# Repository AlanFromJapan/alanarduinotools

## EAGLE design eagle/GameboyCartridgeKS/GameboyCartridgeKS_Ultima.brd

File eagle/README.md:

The content of this folder was moved to another repository for clarity reason on May 29th 2020.
On the same Git account, the repository is **pcb-design**.

Here : https://github.com/AlanFromJapan/pcb-design

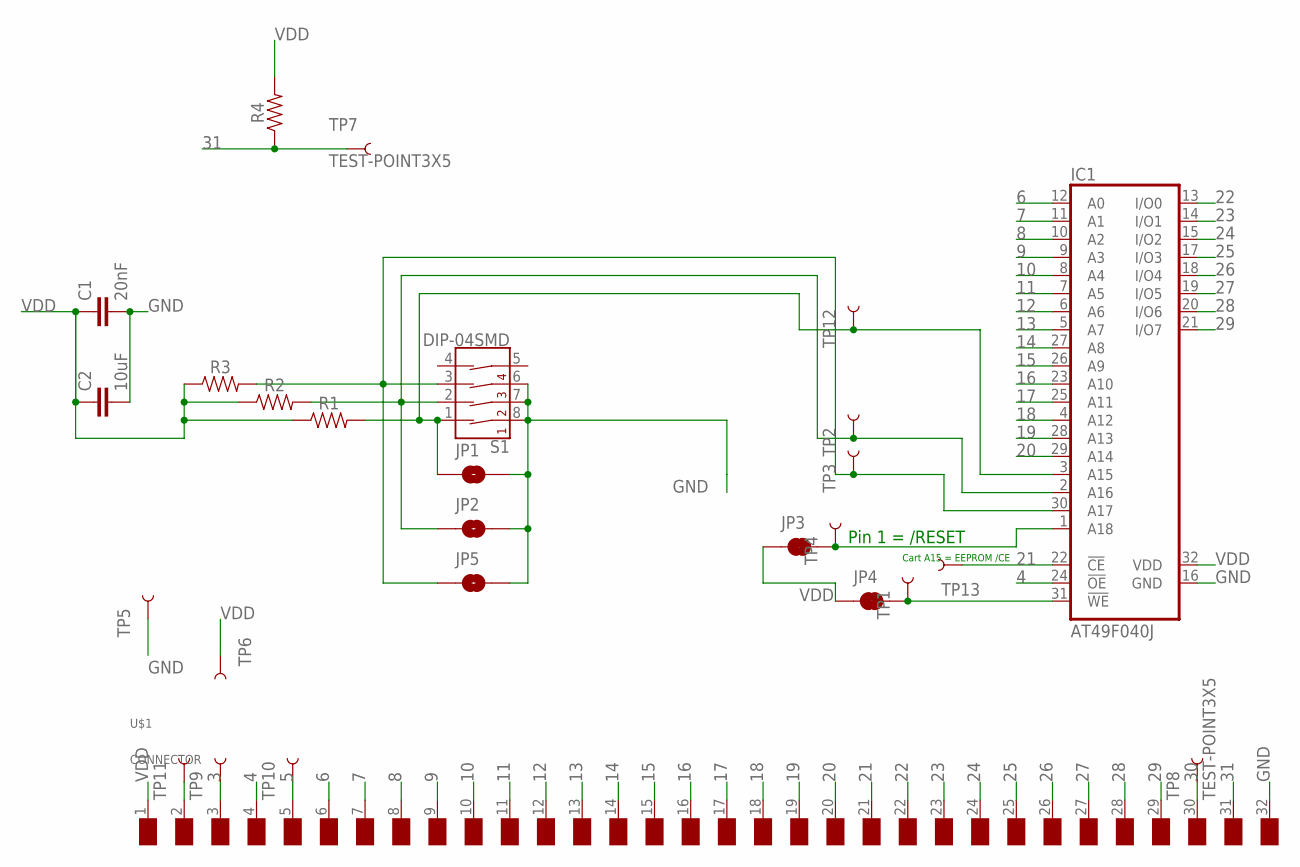
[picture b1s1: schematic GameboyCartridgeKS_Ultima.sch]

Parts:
C1: 20nF; C0805
C2: 10uF; 1206
IC1: AT49F040J; PLCC32R
JP1, JP2, JP5: JUMPER-SMT_2_NO_NO-SILK; SMT-JUMPER_2_NO_NO-SILK
JP3, JP4: JUMPER-SMT_2_NC_TRACE_SILK; SMT-JUMPER_2_NC_TRACE_SILK
R1, R2, R3, R4: 1206
S1: DIP-04SMD; DIPSWITCH-04-SMD
TP1, TP2, TP3, TP4, TP5, TP6, TP7, TP8, TP9, TP10, TP11, TP12, TP13: TEST-POINT3X5; PAD.03X.05
U$1: CONNECTOR

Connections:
3: TP9.P$1, U$1.3 (/WR)
4: IC1.24 (!OE), U$1.4 (/RD)
5: TP10.P$1, U$1.5 (/RCS)
6: IC1.12 (A0), U$1.6 (A0)
7: IC1.11 (A1), U$1.7 (A1)
8: IC1.10 (A2), U$1.8 (A2)
9: IC1.9 (A3), U$1.9 (A3)
10: IC1.8 (A4), U$1.10 (A4)
11: IC1.7 (A5), U$1.11 (A5)
12: IC1.6 (A6), U$1.12 (A6)
13: IC1.5 (A7), U$1.13 (A7)
14: IC1.27 (A8), U$1.14 (A8)
15: IC1.26 (A9), U$1.15 (A9)
16: IC1.23 (A10), U$1.16 (A10)
17: IC1.25 (A11), U$1.17 (A11)
18: IC1.4 (A12), U$1.18 (A12)
19: IC1.28 (A13), U$1.19 (A13)
20: IC1.29 (A14), U$1.20 (A14)
21: IC1.22 (!CE), TP13.P$1, U$1.21 (A15)
22: IC1.13 (I/O0), U$1.22 (D0)
23: IC1.14 (I/O1), U$1.23 (D1)
24: IC1.15 (I/O2), U$1.24 (D2)
25: IC1.17 (I/O3), U$1.25 (D3)
26: IC1.18 (I/O4), U$1.26 (D4)
27: IC1.19 (I/O5), U$1.27 (D5)
28: IC1.20 (I/O6), U$1.28 (D6)
29: IC1.21 (I/O7), U$1.29 (D7)
30: TP8.P$1, U$1.30 (/RS)
31: R4.1, TP7.P$1, U$1.31 (VIN)
GND: C1.2, C2.2, IC1.16 (GND), JP1.2, JP2.2, JP5.2, S1.6 (3B), S1.7 (2B), S1.8 (1B), TP5.P$1, U$1.32 (GND)
unnamed: IC1.31 (!WE), JP4.2, TP1.P$1
unnamed: TP11.P$1, U$1.2 (NC)
unnamed: IC1.3 (A15), JP1.1, R1.2, S1.1 (1A), TP12.P$1
unnamed: IC1.1 (A18), JP3.2, TP4.P$1
unnamed: IC1.2 (A16), JP2.1, R2.2, S1.2 (2A), TP2.P$1
unnamed: IC1.30 (A17), JP5.1, R3.2, S1.3 (3A), TP3.P$1
VDD: C1.1, C2.1, IC1.32 (VDD), JP3.1, JP4.1, R1.1, R2.1, R3.1, R4.2, TP6.P$1, U$1.1 (VDD)

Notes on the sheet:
Pin 1 = /RESET
Cart A15 = EEPROM /CE

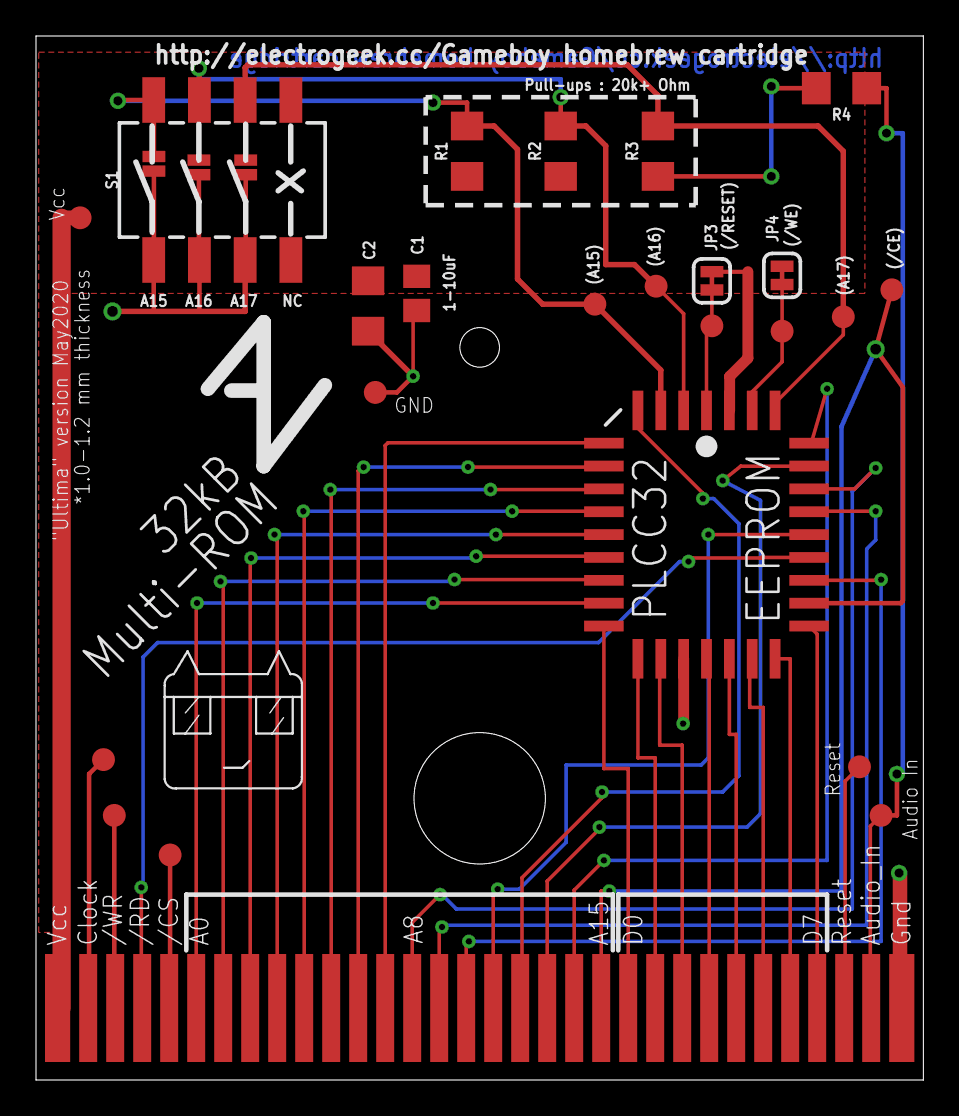
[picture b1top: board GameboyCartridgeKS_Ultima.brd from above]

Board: 2 copper layers, 49.3 x 58.0 mm, 29 parts (0 on the bottom side), 37 nets.

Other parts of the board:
U$2: GAMEBOY_LOGO
U$3: PIGMAN1

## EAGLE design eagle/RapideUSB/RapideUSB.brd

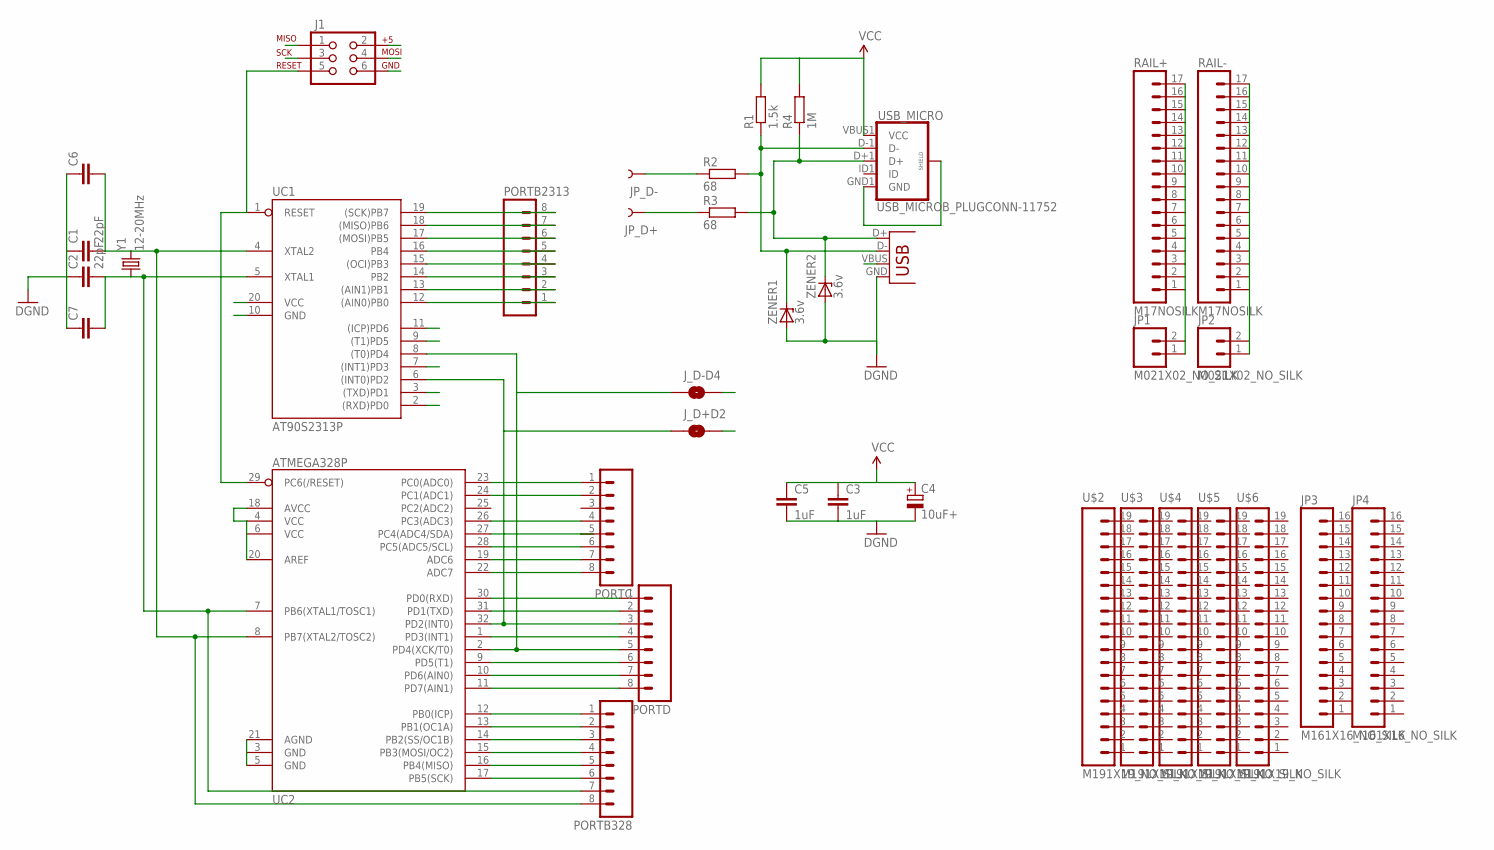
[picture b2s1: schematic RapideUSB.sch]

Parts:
C1, C2: 22pF; C025-024X044
C3, C5: 1uF; C025-024X044
C4: 10uF+; E2-5
C6, C7: C-EUC1206K; C1206K
J1: AVR_SPI_PRG_6PTH; 2X3
JP1, JP2: M021X02_NO_SILK; 1X02_NO_SILK
JP3, JP4: M161X16_NO_SILK; 1X16_NO_SILK
JP_D+: TEST-POINT3X5; PAD.03X.05
JP_D-: TEST-POINT3X5; PAD.03X.05
J_D+D2: JUMPER-PAD-2-NOYES_SILK; PAD-JUMPER-2-NO_YES_SILK
J_D-D4: JUMPER-PAD-2-NOYES_SILK; PAD-JUMPER-2-NO_YES_SILK
PORTB328, PORTB2313: M081X08; 1X08
PORTC: M081X08; 1X08
PORTD: M081X08; 1X08
R1: 1.5k; 0204V
R2, R3: 68; 0204V
R4: 1M; 0204V
RAIL+: M17NOSILK; 1X17_NO_SILK
RAIL-: M17NOSILK; 1X17_NO_SILK
U$2, U$3, U$4, U$5, U$6: M191X19_NO_SILK; 1X19_NO_SILK
UC1: AT90S2313P; DIL20
UC2: ATMEGA328P; TQFP32-08
USB_MICRO: USB_MICROB_PLUGCONN-11752; USB-B-MICRO-SMD_V03
USB_MINI: USBSMD; USB-MINIB
Y1: 12-20MHz; HC49U-V
ZENER1, ZENER2: 3.6v; ZDIO-2.5

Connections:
B0: PORTB328.1, UC2.12 (PB0(ICP))
B1: PORTB328.2, UC2.13 (PB1(OC1A))
B2: PORTB328.3, UC2.14 (PB2(SS/OC1B))
B6: C2.2, C7.2, PORTB328.7, UC1.5 (XTAL1), UC2.7 (PB6(XTAL1/TOSC1)), Y1.1
B7: C1.2, C6.2, PORTB328.8, UC1.4 (XTAL2), UC2.8 (PB7(XTAL2/TOSC2)), Y1.2
D0: PORTD.1, UC1.2 ((RXD)PD0), UC2.30 (PD0(RXD))
D1: PORTD.2, UC1.3 ((TXD)PD1), UC2.31 (PD1(TXD))
D2: J_D+D2.1, PORTD.3, UC1.6 ((INT0)PD2), UC2.32 (PD2(INT0))
D3: PORTD.4, UC1.7 ((INT1)PD3), UC2.1 (PD3(INT1))
D4: J_D-D4.1, PORTD.5, UC1.8 ((T0)PD4), UC2.2 (PD4(XCK/T0))
D5: PORTD.6, UC1.9 ((T1)PD5), UC2.9 (PD5(T1))
D6: PORTD.7, UC1.11 ((ICP)PD6), UC2.10 (PD6(AIN0))
D7: PORTD.8, UC2.11 (PD7(AIN1))
D+: JP_D+.P$1, J_D+D2.2, R3.1
D-: JP_D-.P$1, J_D-D4.2, R2.1
GND: C1.1, C2.1, C3.2, C4.-, C5.2, C6.1, C7.1, J1.6, JP2.1, JP2.2, RAIL-.1, RAIL-.2, RAIL-.3, RAIL-.4, RAIL-.5, RAIL-.6, RAIL-.7, RAIL-.8, RAIL-.9, RAIL-.10, RAIL-.11, RAIL-.12, RAIL-.13, RAIL-.14, RAIL-.15, RAIL-.16, RAIL-.17, UC1.10 (GND), UC2.3 (GND), UC2.5 (GND), UC2.21 (AGND), USB_MICRO.GND1 (GND), USB_MICRO.SHIELD1 (SHIELD), USB_MICRO.SHIELD2 (SHIELD), USB_MICRO.SHIELD3 (SHIELD), USB_MINI.GND, ZENER1.A, ZENER2.A
MISO: J1.1, PORTB328.5, PORTB2313.7, UC1.18 ((MISO)PB6), UC2.16 (PB4(MISO))
MOSI: J1.4, PORTB328.4, PORTB2313.6, UC1.17 ((MOSI)PB5), UC2.15 (PB3(MOSI/OC2))
unnamed: PORTB2313.5, UC1.16 (PB4)
unnamed: PORTB2313.4, UC1.15 ((OCI)PB3)
unnamed: PORTB2313.3, UC1.14 (PB2)
unnamed: PORTB2313.2, UC1.13 ((AIN1)PB1)
unnamed: PORTC.1, UC2.23 (PC0(ADC0))
unnamed: PORTC.2, UC2.24 (PC1(ADC1))
unnamed: PORTC.4, UC2.26 (PC3(ADC3))
unnamed: PORTC.5, UC2.27 (PC4(ADC4/SDA))
unnamed: PORTC.6, UC2.28 (PC5(ADC5/SCL))
unnamed: PORTC.7, UC2.19 (ADC6)
unnamed: PORTC.8, UC2.22 (ADC7)
unnamed: PORTB2313.1, UC1.12 ((AIN0)PB0)
RESET: J1.5, UC1.1 (RESET), UC2.29 (PC6(/RESET))
SCK: J1.3, PORTB328.6, PORTB2313.8, UC1.19 ((SCK)PB7), UC2.17 (PB5(SCK))
USBD+: R3.2, R4.1, USB_MICRO.D+1 (D+), USB_MINI.D+, ZENER2.C
USBD-: R1.1, R2.2, USB_MICRO.D-1 (D-), USB_MINI.D-, ZENER1.C
VCC: C3.1, C4.+, C5.1, J1.2, JP1.1, JP1.2, R1.2, R4.2, RAIL+.1, RAIL+.2, RAIL+.3, RAIL+.4, RAIL+.5, RAIL+.6, RAIL+.7, RAIL+.8, RAIL+.9, RAIL+.10, RAIL+.11, RAIL+.12, RAIL+.13, RAIL+.14, RAIL+.15, RAIL+.16, RAIL+.17, UC1.20 (VCC), UC2.4 (VCC), UC2.6 (VCC), UC2.18 (AVCC), UC2.20 (AREF), USB_MICRO.VBUS1 (VCC), USB_MINI.VBUS

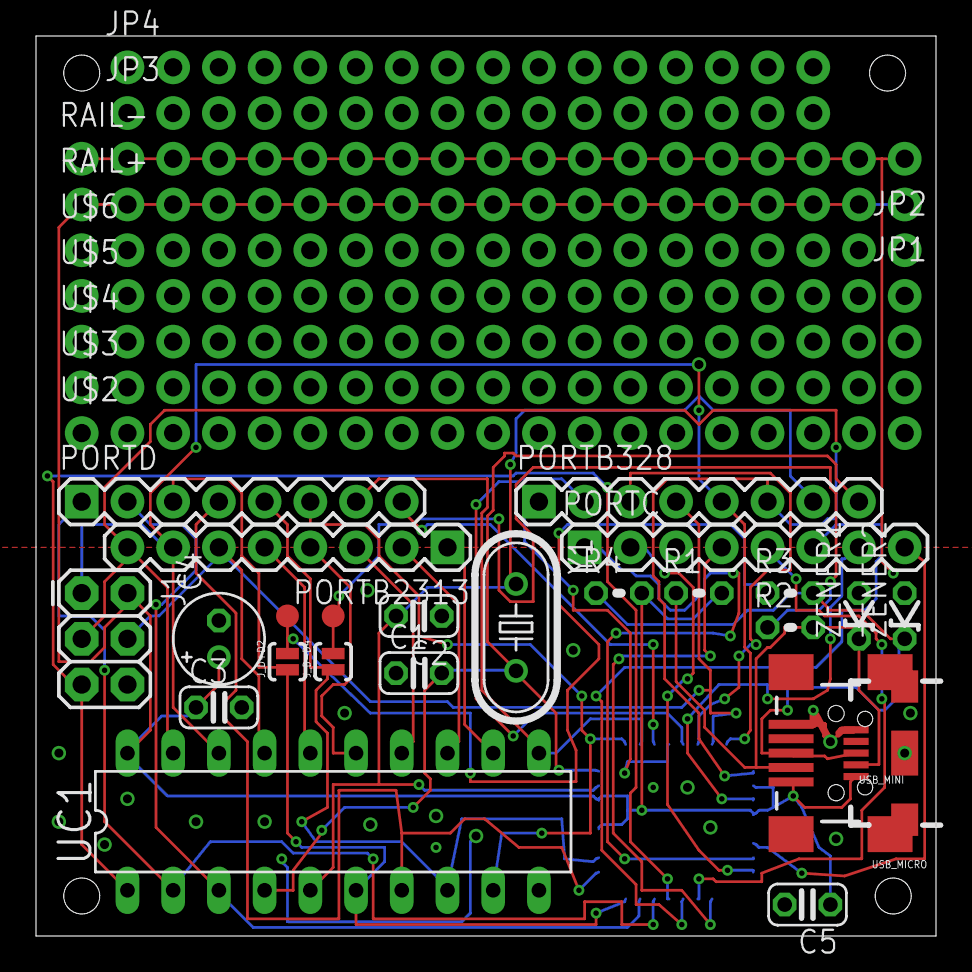
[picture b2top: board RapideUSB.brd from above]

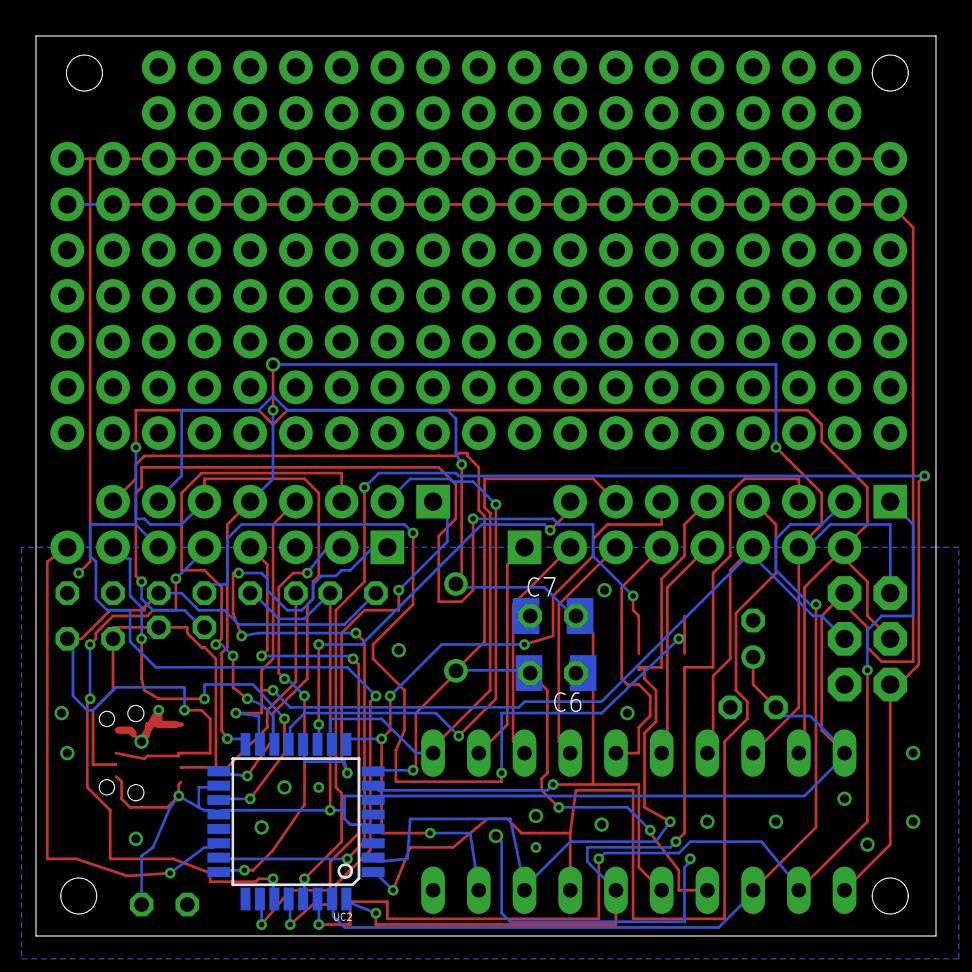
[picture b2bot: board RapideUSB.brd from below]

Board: 2 copper layers, 50.0 x 50.0 mm, 39 parts (3 on the bottom side), 35 nets.

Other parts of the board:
U$1: VUSB_LOGO

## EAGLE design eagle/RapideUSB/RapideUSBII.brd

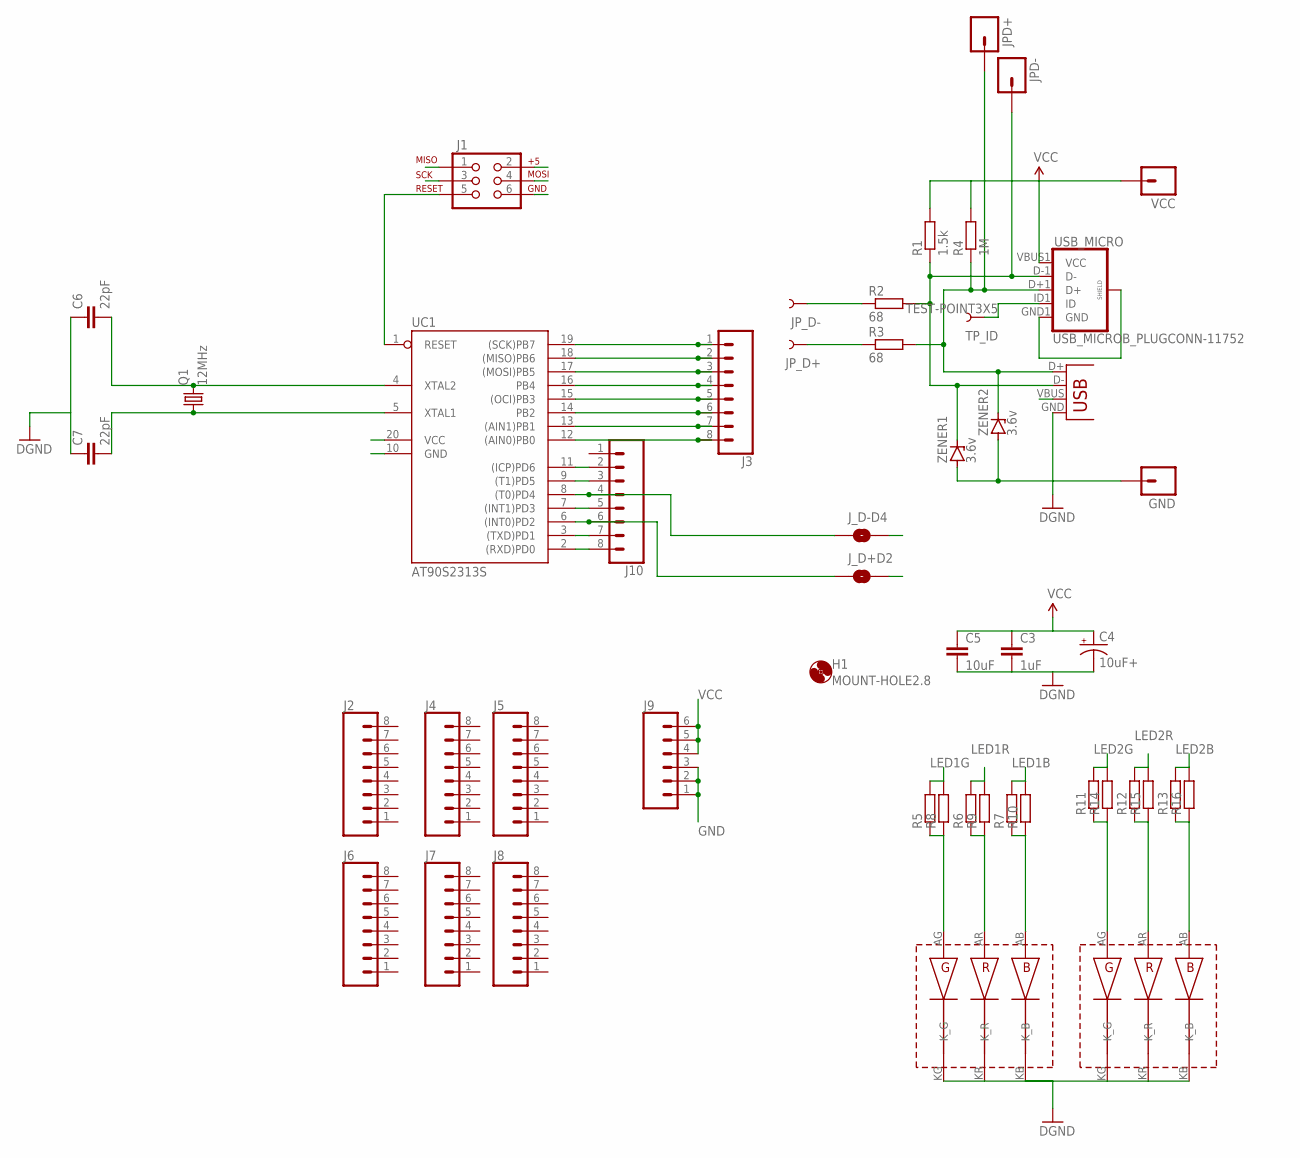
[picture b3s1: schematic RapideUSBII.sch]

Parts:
C3: 1uF; 1206
C4: 10uF+; PANASONIC_E
C5: 10uF; 0805
C6, C7: 22pF; 1206
GND: M01PTH_NO_SILK_YES_STOP; 1X01_NO_SILK
H1: MOUNT-HOLE2.8; 2,8
J1: AVR_SPI_PRG_6PTH; 2X3
J2, J4, J5, J6, J7, J8: CONN_08NO_SILK_FEMALE_PTH; 1X08_NO_SILK
J3: CONN_08SMD-STRAIGHT-ALT-FEMALE; 1X08_SMD_ALT
J9: CONN_06NO_SILK_FEMALE_PTH; 1X06_NO_SILK
J10: CONN_08SMD-STRAIGHT-FEMALE; 1X08_SMD
JPD+: M01PTH_NO_SILK_YES_STOP; 1X01_NO_SILK
JPD-: M01PTH_NO_SILK_YES_STOP; 1X01_NO_SILK
JP_D+: TEST-POINT3X5; PAD.03X.05
JP_D-: TEST-POINT3X5; PAD.03X.05
J_D+D2: JUMPER-PAD-2-NOYES_SILK; PAD-JUMPER-2-NO_YES_SILK
J_D-D4: JUMPER-PAD-2-NOYES_SILK; PAD-JUMPER-2-NO_YES_SILK
LED1: RGB-SMT-SQUARE6X6MM; SMT-SQUARE6
LED2: RGB-SMT-SQUARE5X5MM; SMT-SQUARE5
Q1: 12MHz; HC49U
R1: 1.5k; 0204V
R2, R3: 68; 0204V
R4: 1M; 0204V
R5, R6, R7, R11, R12, R13: R-EU_0204/2V; 0204V
R8, R9, R10, R14, R15, R16: R-EU_M1206; M1206
TP_ID: TEST-POINT3X5; PAD.03X.05
UC1: AT90S2313S; SO20L
USB_MICRO: USB_MICROB_PLUGCONN-11752; USB-B-MICRO-SMD_V03
USB_MINI: USBSMD; USB-MINIB
VCC: M01PTH_NO_SILK_YES_STOP; 1X01_NO_SILK
ZENER1, ZENER2: 3.6v; ZDIO-2.5

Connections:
D0: J10.8, UC1.2 ((RXD)PD0)
D1: J10.7, UC1.3 ((TXD)PD1)
D2: J10.6, J_D+D2.1, UC1.6 ((INT0)PD2)
D3: J10.5, UC1.7 ((INT1)PD3)
D4: J10.4, J_D-D4.1, UC1.8 ((T0)PD4)
D+: JP_D+.P$1, J_D+D2.2, R3.1
D-: JP_D-.P$1, J_D-D4.2, R2.1
GND: C3.2, C4.-, C5.2, C6.1, C7.1, GND.1, J1.6, J9.1, J9.2, J9.3, LED1.KB (K_B), LED1.KG (K_G), LED1.KR (K_R), LED2.KB (K_B), LED2.KG (K_G), LED2.KR (K_R), UC1.10 (GND), USB_MICRO.GND1 (GND), USB_MICRO.SHIELD1 (SHIELD), USB_MICRO.SHIELD2 (SHIELD), USB_MICRO.SHIELD3 (SHIELD), USB_MINI.GND, ZENER1.A, ZENER2.A
LED1B: J3.8, R7.2, R10.2, UC1.12 ((AIN0)PB0)
LED1G: J10.2, R5.2, R8.2, UC1.11 ((ICP)PD6)
LED1R: J10.3, R6.2, R9.2, UC1.9 ((T1)PD5)
LED2B: J3.5, R13.2, R16.2, UC1.15 ((OCI)PB3)
LED2G: J3.6, R11.2, R14.2, UC1.14 (PB2)
LED2R: J3.7, R12.2, R15.2, UC1.13 ((AIN1)PB1)
MISO: J1.1, J3.2, UC1.18 ((MISO)PB6)
MOSI: J1.4, J3.3, UC1.17 ((MOSI)PB5)
unnamed: J3.4, UC1.16 (PB4)
unnamed: TP_ID.P$1, USB_MICRO.ID1 (ID)
unnamed: LED1.AG (ANODE_G), R5.1, R8.1
unnamed: LED1.AR (ANODE_R), R6.1, R9.1
unnamed: LED1.AB (ANODE_B), R7.1, R10.1
unnamed: LED2.AG (ANODE_G), R11.1, R14.1
unnamed: LED2.AR (ANODE_R), R12.1, R15.1
unnamed: LED2.AB (ANODE_B), R13.1, R16.1
unnamed: C7.2, Q1.1, UC1.5 (XTAL1)
unnamed: C6.2, Q1.2, UC1.4 (XTAL2)
RESET: J1.5, UC1.1 (RESET)
SCK: J1.3, J3.1, UC1.19 ((SCK)PB7)
USBD+: JPD+.1, R3.2, R4.1, USB_MICRO.D+1 (D+), USB_MINI.D+, ZENER2.C
USBD-: JPD-.1, R1.1, R2.2, USB_MICRO.D-1 (D-), USB_MINI.D-, ZENER1.C
VCC: C3.1, C4.+, C5.1, J1.2, J9.4, J9.5, J9.6, R1.2, R4.2, UC1.20 (VCC), USB_MICRO.VBUS1 (VCC), USB_MINI.VBUS, VCC.1

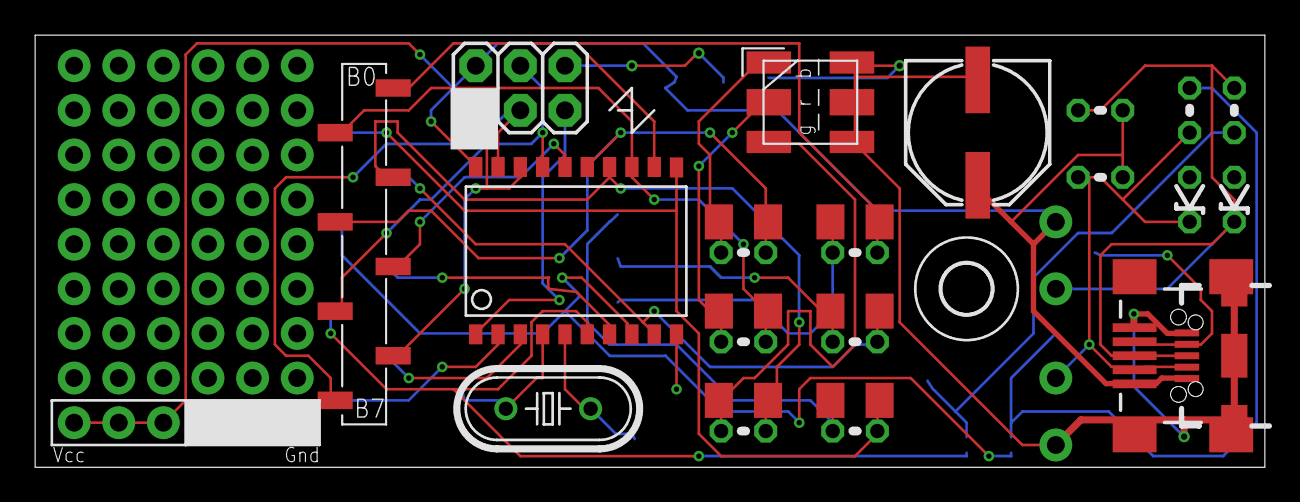
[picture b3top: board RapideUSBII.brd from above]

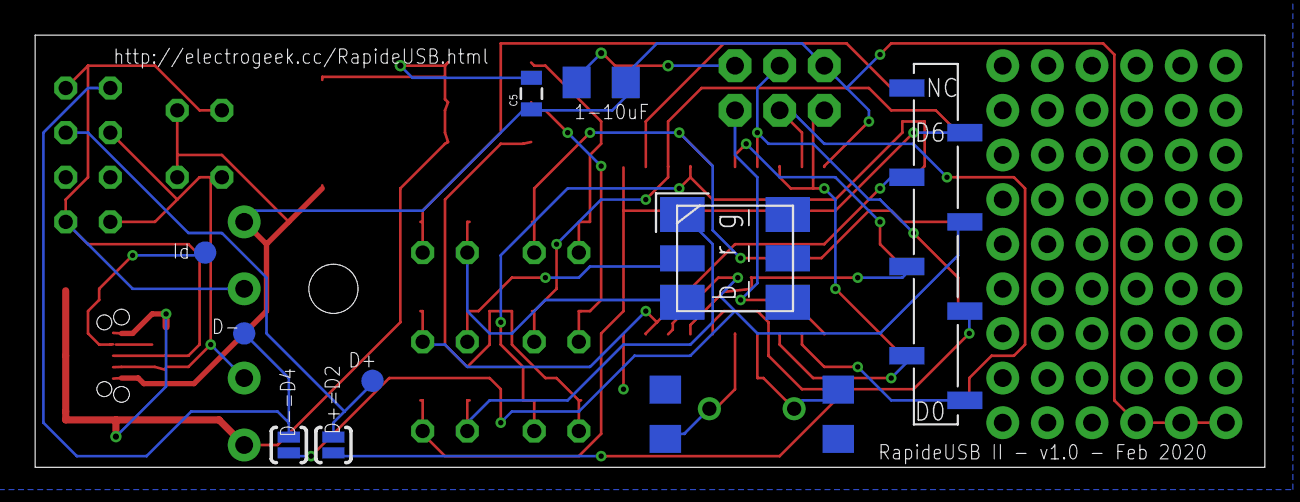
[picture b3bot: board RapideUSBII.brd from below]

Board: 2 copper layers, 70.0 x 24.6 mm, 50 parts (12 on the bottom side), 31 nets.

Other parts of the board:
U$1: VUSB_LOGO

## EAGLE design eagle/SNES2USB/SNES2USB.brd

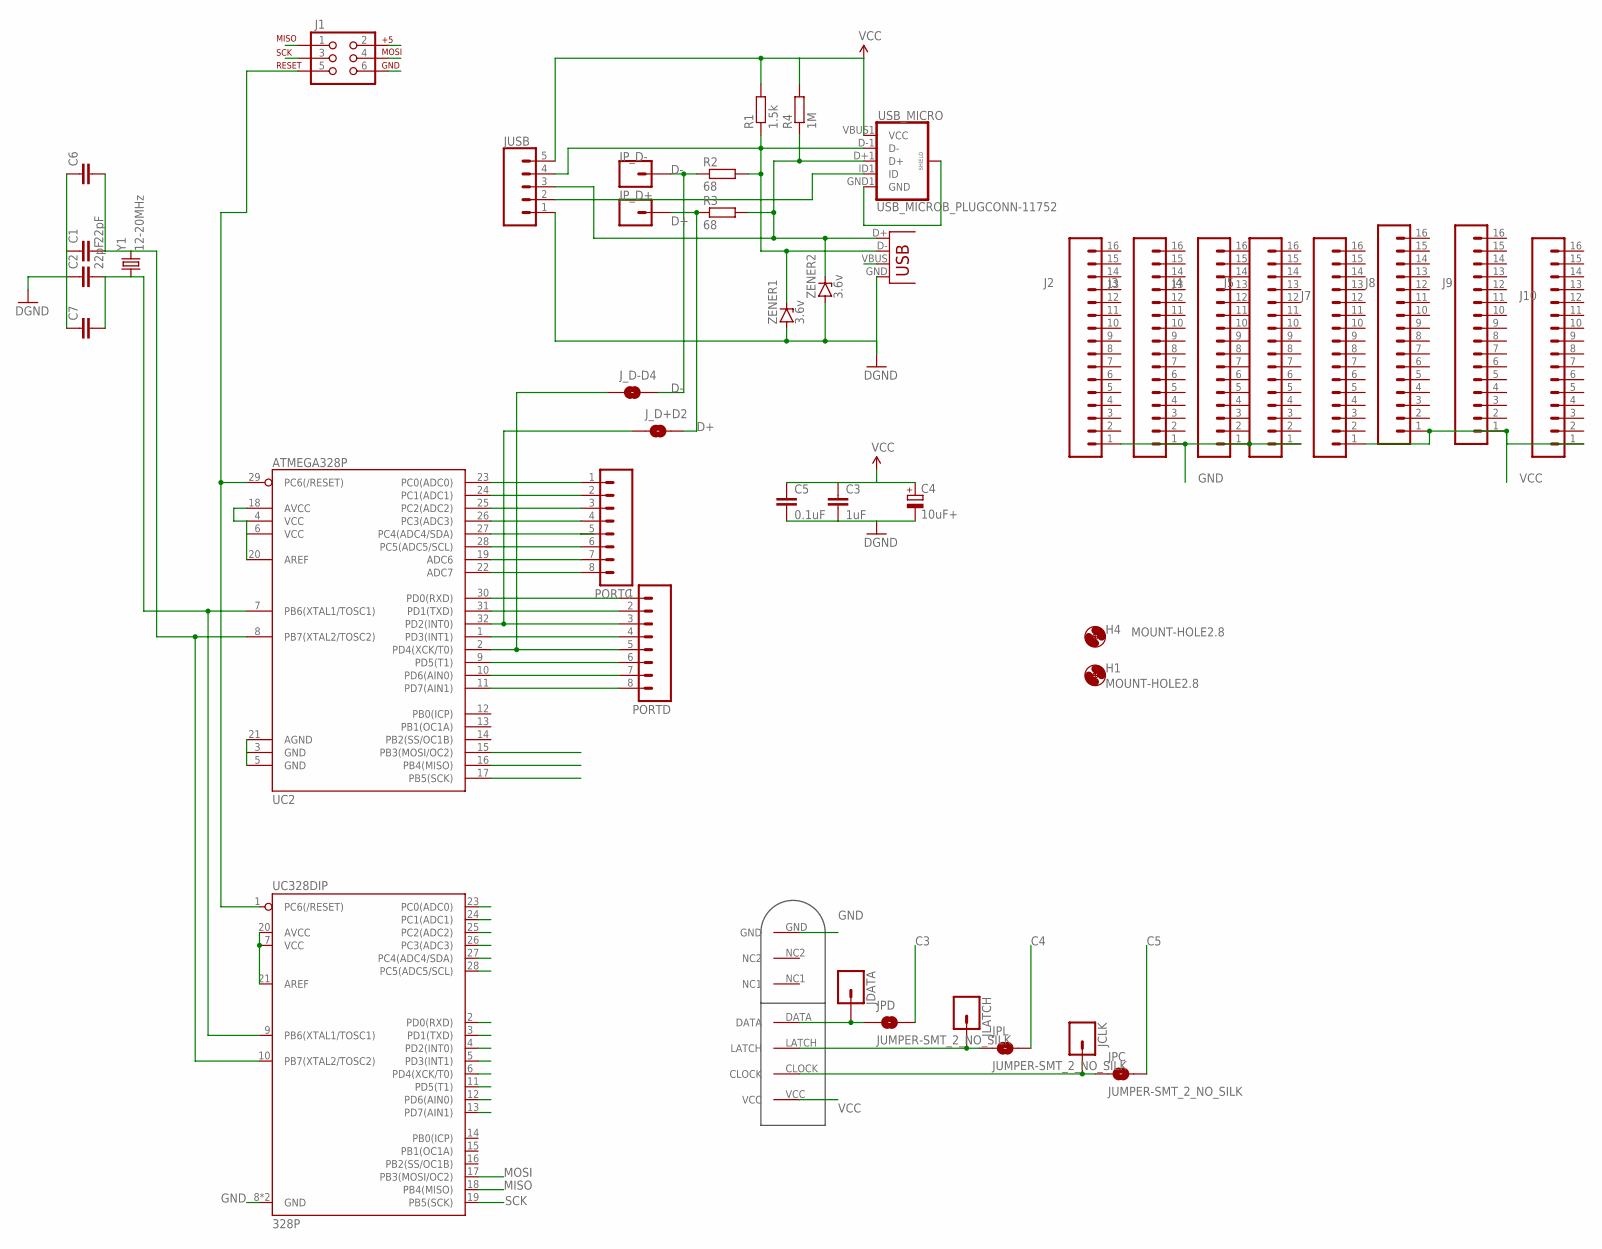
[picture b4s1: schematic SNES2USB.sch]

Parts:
C1, C2: 22pF; C025-024X044
C3: 1uF; C025-024X044
C4: 10uF+; E2-5
C5: 0.1uF; C025-024X044
C6, C7: C-EUC1206K; C1206K
H1, H4: MOUNT-HOLE2.8; 2,8
J1: AVR_SPI_PRG_6PTH; 2X3
J2, J3, J4, J5, J7, J8, J9, J10: CONN_161X16_NO_SILK; 1X16_NO_SILK
JCLK: CONN_01PTH_NO_SILK_YES_STOP; 1X01_NO_SILK
JDATA: CONN_01PTH_NO_SILK_YES_STOP; 1X01_NO_SILK
JLATCH: CONN_01PTH_NO_SILK_YES_STOP; 1X01_NO_SILK
JPC: JUMPER-SMT_2_NO_SILK; SMT-JUMPER_2_NO_SILK
JPD: JUMPER-SMT_2_NO_SILK; SMT-JUMPER_2_NO_SILK
JPL: JUMPER-SMT_2_NO_SILK; SMT-JUMPER_2_NO_SILK
JP_D+: CONN_01PTH_NO_SILK_YES_STOP; 1X01_NO_SILK
JP_D-: CONN_01PTH_NO_SILK_YES_STOP; 1X01_NO_SILK
JUSB: CONN_05; 1X05
J_D+D2: JUMPER-PAD-2-NOYES_SILK; PAD-JUMPER-2-NO_YES_SILK
J_D-D4: JUMPER-PAD-2-NOYES_SILK; PAD-JUMPER-2-NO_YES_SILK
PORTC: M081X08; 1X08
PORTD: M081X08; 1X08
R1: 1.5k; 0204V
R2, R3: 68; 0204V
R4: 1M; 0204V
U$1: SNES_JOYPAD_CONNECTOR; SNES_PAD
UC2: ATMEGA328P; TQFP32-08
UC328DIP: 328P; DIP28
USB_MICRO: USB_MICROB_PLUGCONN-11752; USB-B-MICRO-SMD_V03
USB_MINI: USBSMD; USB-MINIB
Y1: 12-20MHz; HC49U-V
ZENER1, ZENER2: 3.6v; ZDIO-2.5

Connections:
B6: C2.2, C7.2, UC2.7 (PB6(XTAL1/TOSC1)), UC328DIP.9 (PB6(XTAL1/TOSC1)), Y1.1
B7: C1.2, C6.2, UC2.8 (PB7(XTAL2/TOSC2)), UC328DIP.10 (PB7(XTAL2/TOSC2)), Y1.2
C0: PORTC.1, UC2.23 (PC0(ADC0)), UC328DIP.23 (PC0(ADC0))
C1: PORTC.2, UC2.24 (PC1(ADC1)), UC328DIP.24 (PC1(ADC1))
C2: UC328DIP.25 (PC2(ADC2))
C3: JPD.2, PORTC.4, UC2.26 (PC3(ADC3)), UC328DIP.26 (PC3(ADC3))
C4: JPL.2, PORTC.5, UC2.27 (PC4(ADC4/SDA)), UC328DIP.27 (PC4(ADC4/SDA))
C5: JPC.2, PORTC.6, UC2.28 (PC5(ADC5/SCL)), UC328DIP.28 (PC5(ADC5/SCL))
D0: PORTD.1, UC2.30 (PD0(RXD)), UC328DIP.2 (PD0(RXD))
D1: PORTD.2, UC2.31 (PD1(TXD)), UC328DIP.3 (PD1(TXD))
D2: J_D+D2.1, PORTD.3, UC2.32 (PD2(INT0)), UC328DIP.4 (PD2(INT0))
D3: PORTD.4, UC2.1 (PD3(INT1)), UC328DIP.5 (PD3(INT1))
D4: J_D-D4.1, PORTD.5, UC2.2 (PD4(XCK/T0)), UC328DIP.6 (PD4(XCK/T0))
D5: PORTD.6, UC2.9 (PD5(T1)), UC328DIP.11 (PD5(T1))
D6: PORTD.7, UC2.10 (PD6(AIN0)), UC328DIP.12 (PD6(AIN0))
D7: PORTD.8, UC2.11 (PD7(AIN1)), UC328DIP.13 (PD7(AIN1))
D+: JP_D+.1, J_D+D2.2, R3.1
D-: JP_D-.1, J_D-D4.2, R2.1
GND: C1.1, C2.1, C3.2, C4.-, C5.2, C6.1, C7.1, J1.6, J2.1, J3.1, J4.1, J5.1, JUSB.1, U$1.GND, UC2.3 (GND), UC2.5 (GND), UC2.21 (AGND), UC328DIP.8 (GND), UC328DIP.22 (GND), USB_MICRO.GND1 (GND), USB_MICRO.SHIELD1 (SHIELD), USB_MICRO.SHIELD2 (SHIELD), USB_MICRO.SHIELD3 (SHIELD), USB_MINI.GND, ZENER1.A, ZENER2.A
MISO: J1.1, UC2.16 (PB4(MISO)), UC328DIP.18 (PB4(MISO))
MOSI: J1.4, UC2.15 (PB3(MOSI/OC2)), UC328DIP.17 (PB3(MOSI/OC2))
unnamed: JUSB.2, USB_MICRO.ID1 (ID)
unnamed: JDATA.1, JPD.1, U$1.DATA
unnamed: PORTC.3, UC2.25 (PC2(ADC2))
unnamed: JLATCH.1, JPL.1, U$1.LATCH
unnamed: JCLK.1, JPC.1, U$1.CLOCK
unnamed: PORTC.7, UC2.19 (ADC6)
unnamed: PORTC.8, UC2.22 (ADC7)
RESET: J1.5, UC2.29 (PC6(/RESET)), UC328DIP.1 (PC6(/RESET))
SCK: J1.3, UC2.17 (PB5(SCK)), UC328DIP.19 (PB5(SCK))
USBD+: JUSB.3, R3.2, R4.1, USB_MICRO.D+1 (D+), USB_MINI.D+, ZENER2.C
USBD-: JUSB.4, R1.1, R2.2, USB_MICRO.D-1 (D-), USB_MINI.D-, ZENER1.C
VCC: C3.1, C4.+, C5.1, J1.2, J7.1, J8.1, J9.1, J10.1, JUSB.5, R1.2, R4.2, U$1.VCC, UC2.4 (VCC), UC2.6 (VCC), UC2.18 (AVCC), UC2.20 (AREF), UC328DIP.7 (VCC), UC328DIP.20 (AVCC), UC328DIP.21 (AREF), USB_MICRO.VBUS1 (VCC), USB_MINI.VBUS

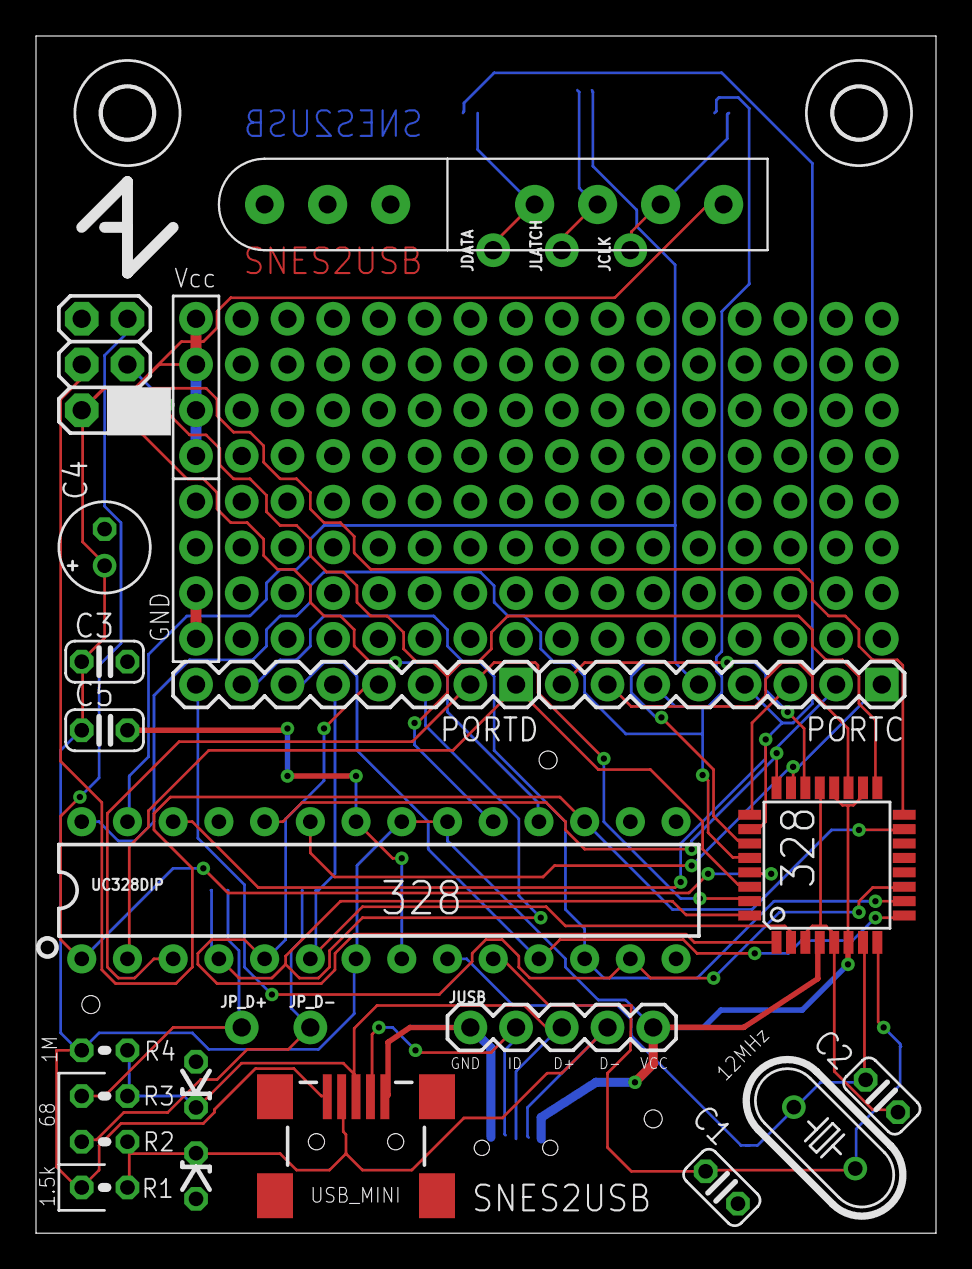
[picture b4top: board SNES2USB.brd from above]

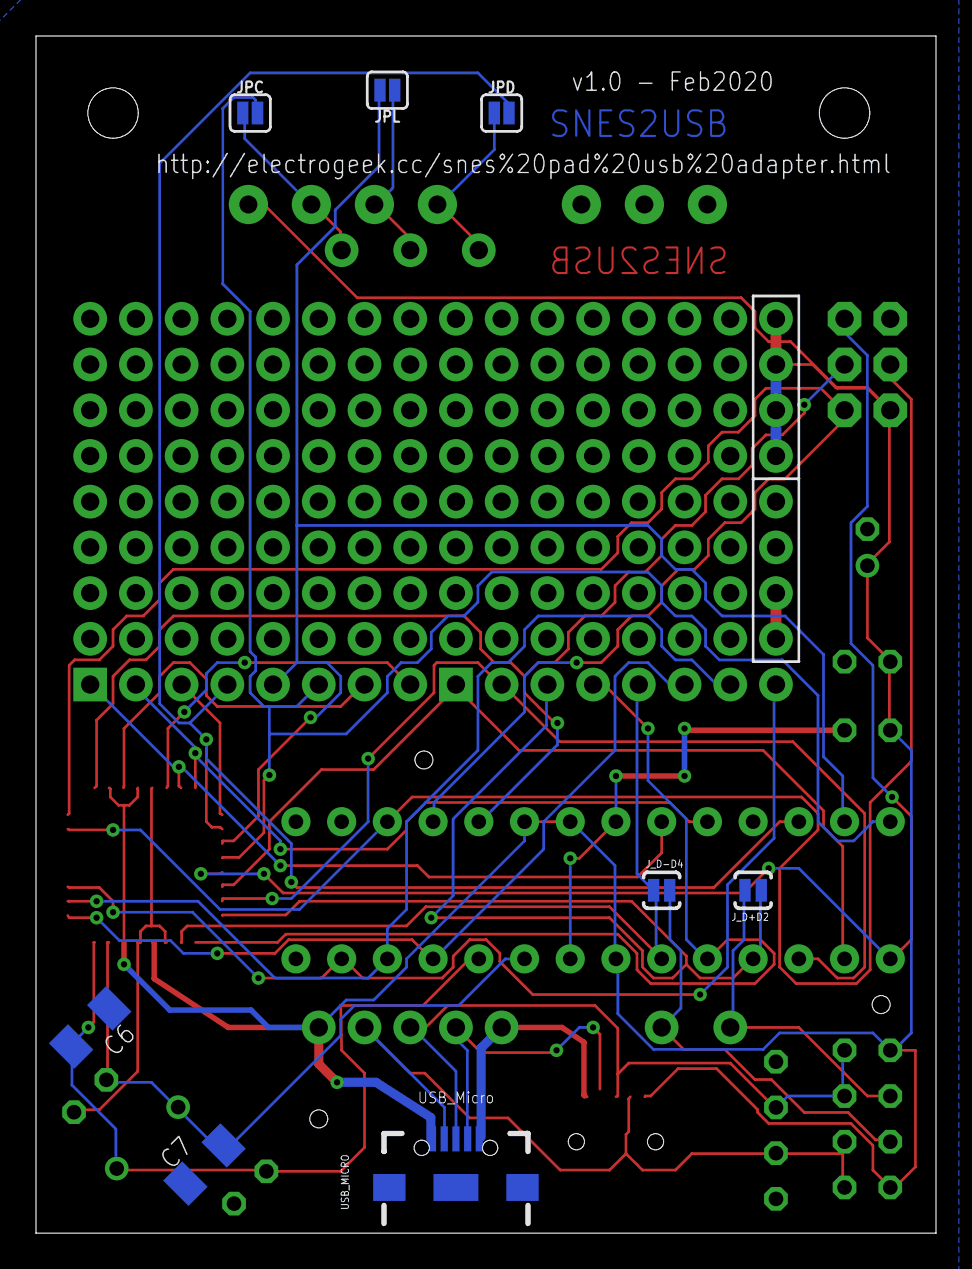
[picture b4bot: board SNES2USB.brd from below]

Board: 2 copper layers, 50.0 x 66.5 mm, 44 parts (8 on the bottom side), 32 nets.

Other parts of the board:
U$2: VUSB_LOGO

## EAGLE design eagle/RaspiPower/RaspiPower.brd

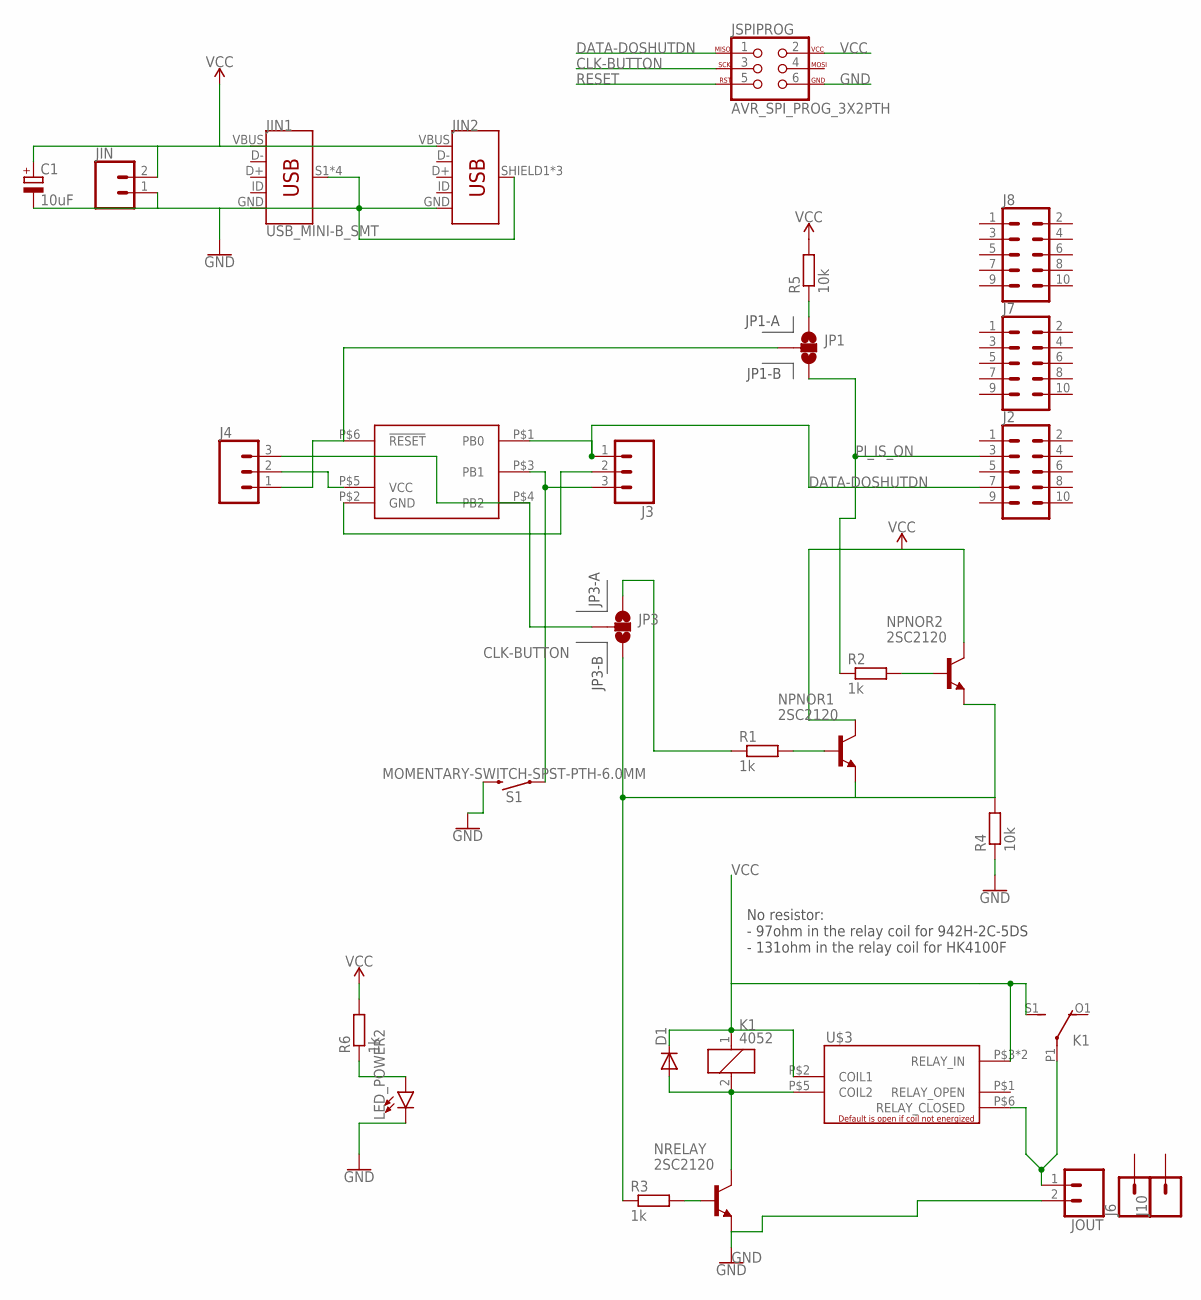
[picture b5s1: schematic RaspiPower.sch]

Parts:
C1: 10uF; E2,5-5
D1: DIODE-D-5; D-5
J2, J7, J8: CONN_05X2PTH; 2X5
J3, J4: CONN_03; 1X03
J6, J10: CONN_01PTH_NO_SILK_YES_STOP; 1X01_NO_SILK
JIN: CONN_02LOCK_LONGPADS; 1X02_LOCK_LONGPADS
JIN1: USB_MINI-B_SMT; USB-MINIB
JIN2: USB_MICRO-B_FEMALE-SMT; USB-B-MICRO-SMD
JOUT: CONN_02LOCK_LONGPADS; 1X02_LOCK_LONGPADS
JP1, JP3: JUMPER-SMT_3_NO_SILK; SMT-JUMPER_3_NO_SILK
JSPIPROG: AVR_SPI_PROG_3X2PTH; 2X3
K1: 4052; F4052
LED_POWER2: LED-FKIT-1206; FKIT-LED-1206
NPNOR1, NPNOR2: 2SC2120; TO92-ECB
NRELAY: 2SC2120; TO92-ECB
R1, R2: 1k; 0207/2V
R3: 1k; 0204/7
R4, R5: 10k; 0207/2V
R6: 1k; R1206W
S1: MOMENTARY-SWITCH-SPST-PTH-6.0MM; TACTILE_SWITCH_PTH_6.0MM
U$1: ATTINY10; SOT23
U$3: HK4100F

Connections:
CLK-BUTTON: J3.3, JSPIPROG.3, S1.1, U$1.P$3 (PB1)
DATA-DOSHUTDN: J2.7, J3.1, JSPIPROG.1, U$1.P$1 (PB0)
GND: C1.-, J3.2, JIN.1, JIN1.GND, JIN1.S1 (SHIELD), JIN1.S2 (SHIELD), JIN1.S3 (SHIELD), JIN1.S4 (SHIELD), JIN2.GND, JIN2.SHIELD1 (SHIELD), JIN2.SHIELD2 (SHIELD), JIN2.SHIELD3 (SHIELD), JOUT.2, JSPIPROG.6, LED_POWER2.C, NRELAY.E, R4.1, S1.3 (2), U$1.P$2 (GND)
unnamed: LED_POWER2.A, R6.1
unnamed: JP3.3, NPNOR1.E, NPNOR2.E, R3.1, R4.2
unnamed: J4.3, JP3.2, U$1.P$4 (PB2)
unnamed: JP1.1, R5.1
unnamed: NRELAY.B, R3.2
unnamed: D1.A, K1.2, NRELAY.C, U$3.P$5 (COIL2)
unnamed: NPNOR1.B, R1.2
unnamed: NPNOR2.B, R2.2
unnamed: JP3.1, R1.1
PI_IS_ON: J2.3, JP1.3, R2.1
RESET: J4.1, JP1.2, JSPIPROG.5, U$1.P$6 (!RESET)
VCC: C1.+, D1.C, J4.2, JIN.2, JIN1.VBUS, JIN2.VBUS, JSPIPROG.2, K1.1, K1.S1 (S), NPNOR1.C, NPNOR2.C, R5.2, R6.2, U$1.P$5 (VCC), U$3.P$2 (COIL1), U$3.P$3 (RELAY_IN), U$3.P$4 (RELAY_IN)
VOUT: JOUT.1, K1.P1, U$3.P$6 (RELAY_CLOSED)

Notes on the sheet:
No resistor: - 97ohm in the relay coil for 942H-2C-5DS - 131ohm in the relay coil for HK4100F
JP3-A
JP3-B
JP1-A
JP1-B

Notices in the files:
parts and their libraries:
SparkFun-LED: Licensing: Creative Commons ShareAlike 4.0 International - https://creativecommons.org/licenses/by-sa/4.0
